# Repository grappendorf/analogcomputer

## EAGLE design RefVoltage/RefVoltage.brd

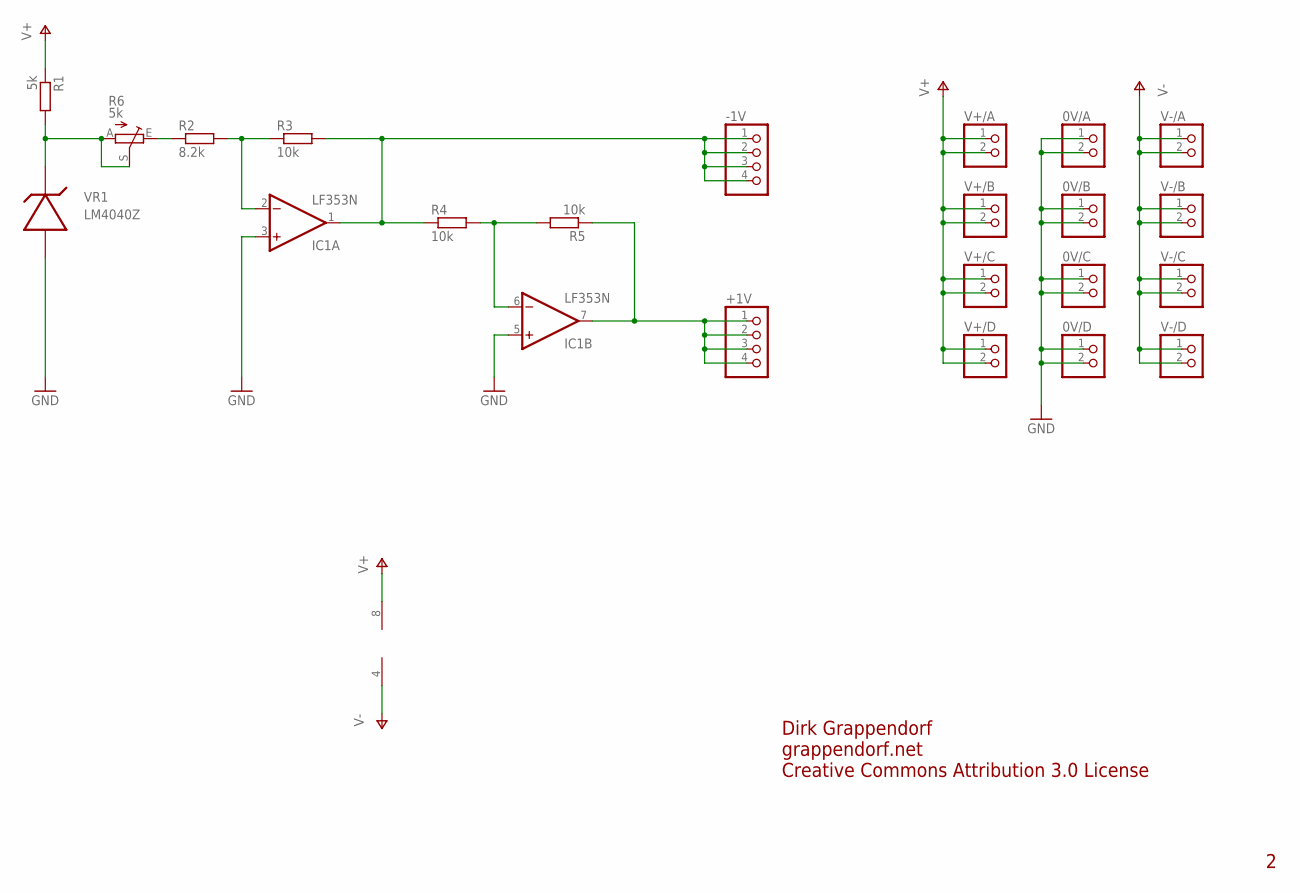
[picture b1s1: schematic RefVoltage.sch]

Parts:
0V/A, 0V/B, 0V/C, 0V/D: PINHD-1X2; 1X02
+1V: PINHD-1X4; 1X04
-1V: PINHD-1X4; 1X04
IC1: LF353N; DIL08
R1: 5k; 0207/7
R2: 8.2k; 0207/7
R3, R4, R5: 10k; 0207/7
R6: 5k; LI10
V+/A: PINHD-1X2; 1X02
V+/B: PINHD-1X2; 1X02
V+/C: PINHD-1X2; 1X02
V+/D: PINHD-1X2; 1X02
V-/A: PINHD-1X2; 1X02
V-/B: PINHD-1X2; 1X02
V-/C: PINHD-1X2; 1X02
V-/D: PINHD-1X2; 1X02
VR1: LM4040Z; TO92

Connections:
GND: 0V/A.1, 0V/A.2, 0V/B.1, 0V/B.2, 0V/C.1, 0V/C.2, 0V/D.1, 0V/D.2, IC1.3 (+IN), IC1.5 (+IN), VR1.3
unnamed: R1.2, R6.A, R6.S, VR1.2
unnamed: IC1.2 (-IN), R2.2, R3.1
unnamed: IC1.6 (-IN), R4.2, R5.2
unnamed: -1V.1, -1V.2, -1V.3, -1V.4, IC1.1 (OUT), R3.2, R4.1
unnamed: +1V.1, +1V.2, +1V.3, +1V.4, IC1.7 (OUT), R5.1
unnamed: R2.1, R6.E
V+: IC1.8 (V+), R1.1, V+/A.1, V+/A.2, V+/B.1, V+/B.2, V+/C.1, V+/C.2, V+/D.1, V+/D.2
V-: IC1.4 (V-), V-/A.1, V-/A.2, V-/B.1, V-/B.2, V-/C.1, V-/C.2, V-/D.1, V-/D.2

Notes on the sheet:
Dirk Grappendorf
grappendorf.net
Creative Commons Attribution 3.0 License

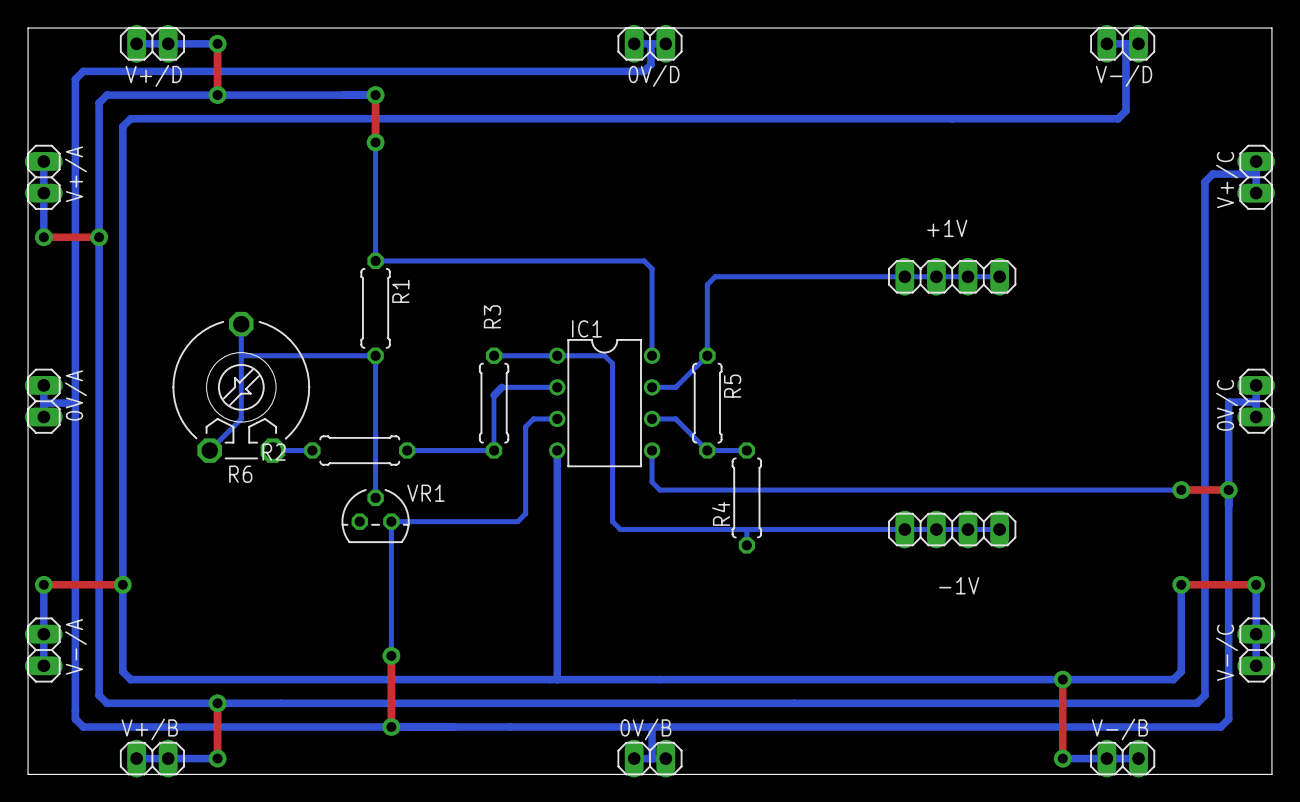
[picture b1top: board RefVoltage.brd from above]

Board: 2 copper layers, 100.0 x 60.0 mm, 22 parts (0 on the bottom side), 9 nets.

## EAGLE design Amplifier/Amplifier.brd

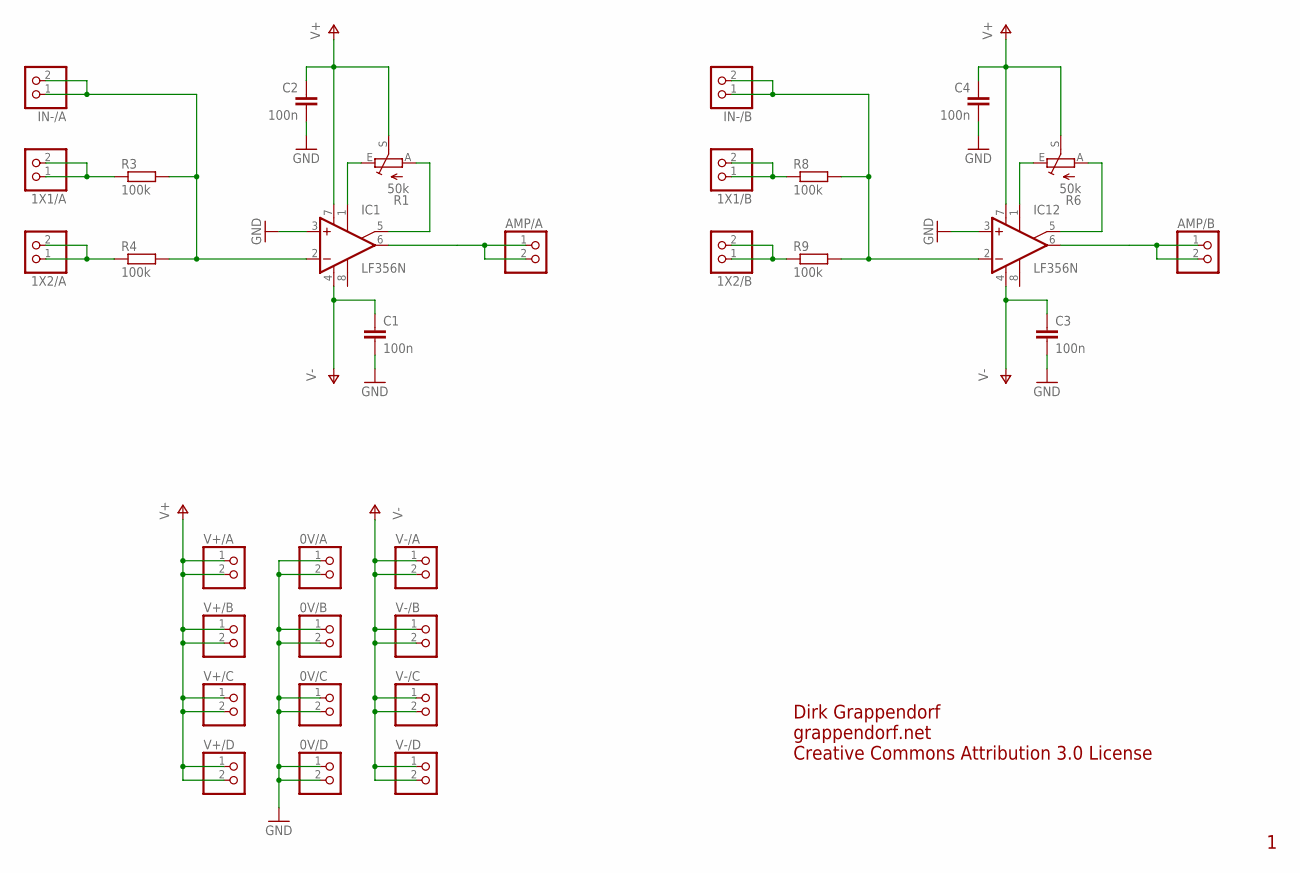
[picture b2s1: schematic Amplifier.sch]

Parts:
0V/A, 0V/B, 0V/C, 0V/D, 1X1/A, 1X1/B, 1X2/A, 1X2/B: PINHD-1X2; 1X02
AMP/A: PINHD-1X2; 1X02
AMP/B: PINHD-1X2; 1X02
C1, C2, C3, C4: 100n; C025-025X050
IC1, IC12: LF356N; DIL08
IN-/A: PINHD-1X2; 1X02
IN-/B: PINHD-1X2; 1X02
R1, R6: 50k; LI15
R3, R4, R8, R9: 100k; 0207/7
V+/A: PINHD-1X2; 1X02
V+/B: PINHD-1X2; 1X02
V+/C: PINHD-1X2; 1X02
V+/D: PINHD-1X2; 1X02
V-/A: PINHD-1X2; 1X02
V-/B: PINHD-1X2; 1X02
V-/C: PINHD-1X2; 1X02
V-/D: PINHD-1X2; 1X02

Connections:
GND: 0V/A.1, 0V/A.2, 0V/B.1, 0V/B.2, 0V/C.1, 0V/C.2, 0V/D.1, 0V/D.2, C1.2, C2.2, C3.2, C4.2, IC1.3 (+IN), IC12.3 (+IN)
unnamed: IC1.1 (ON1), R1.E
unnamed: IC1.5 (ON2), R1.A
unnamed: AMP/A.1, AMP/A.2, IC1.6 (OUT)
unnamed: 1X2/A.1, 1X2/A.2, R4.1
unnamed: 1X1/A.1, 1X1/A.2, R3.1
unnamed: IC1.2 (-IN), IN-/A.1, IN-/A.2, R3.2, R4.2
unnamed: IC12.1 (ON1), R6.E
unnamed: IC12.5 (ON2), R6.A
unnamed: AMP/B.1, AMP/B.2, IC12.6 (OUT)
unnamed: 1X1/B.1, 1X1/B.2, R8.1
unnamed: 1X2/B.1, 1X2/B.2, R9.1
unnamed: IC12.2 (-IN), IN-/B.1, IN-/B.2, R8.2, R9.2
V+: C2.1, C4.1, IC1.7 (V+), IC12.7 (V+), R1.S, R6.S, V+/A.1, V+/A.2, V+/B.1, V+/B.2, V+/C.1, V+/C.2, V+/D.1, V+/D.2
V-: C1.1, C3.1, IC1.4 (V-), IC12.4 (V-), V-/A.1, V-/A.2, V-/B.1, V-/B.2, V-/C.1, V-/C.2, V-/D.1, V-/D.2

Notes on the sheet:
Dirk Grappendorf
grappendorf.net
Creative Commons Attribution 3.0 License

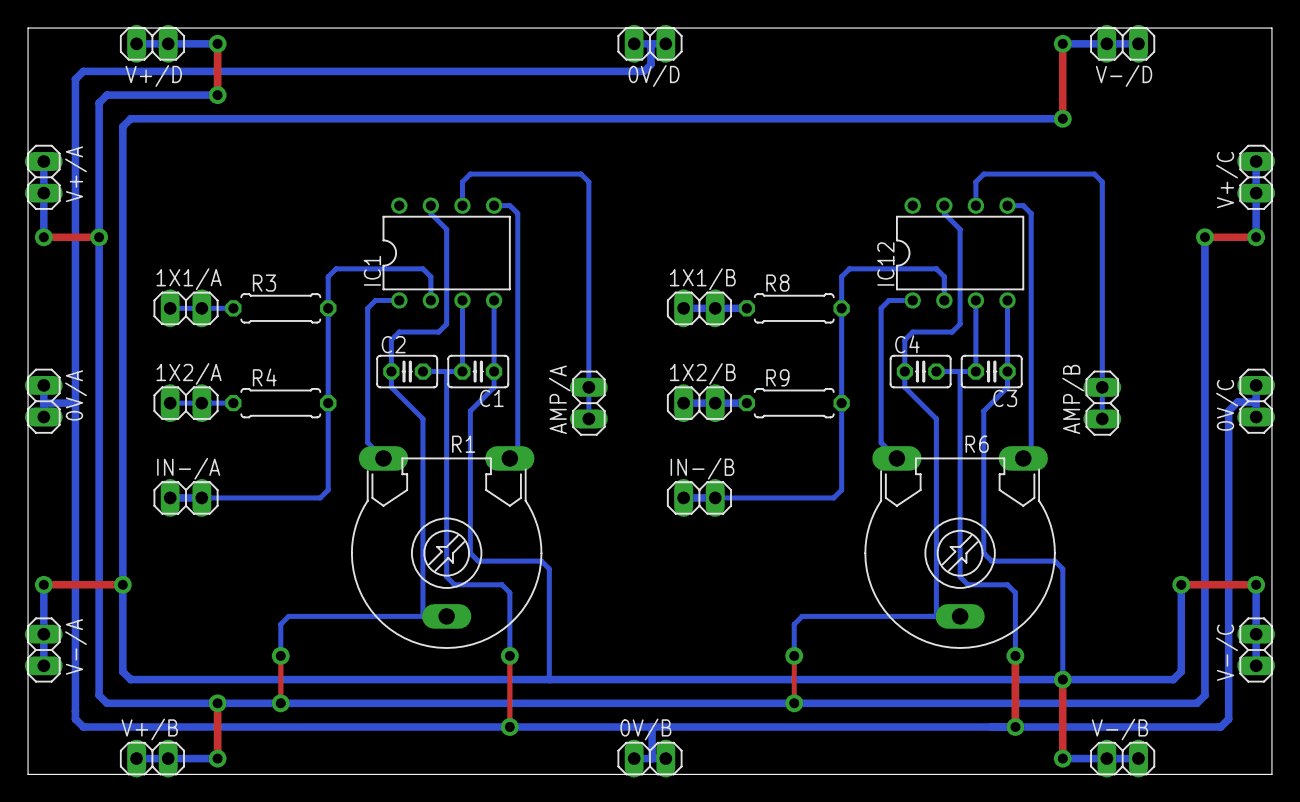
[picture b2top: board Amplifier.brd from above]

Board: 2 copper layers, 100.0 x 60.0 mm, 32 parts (0 on the bottom side), 15 nets.

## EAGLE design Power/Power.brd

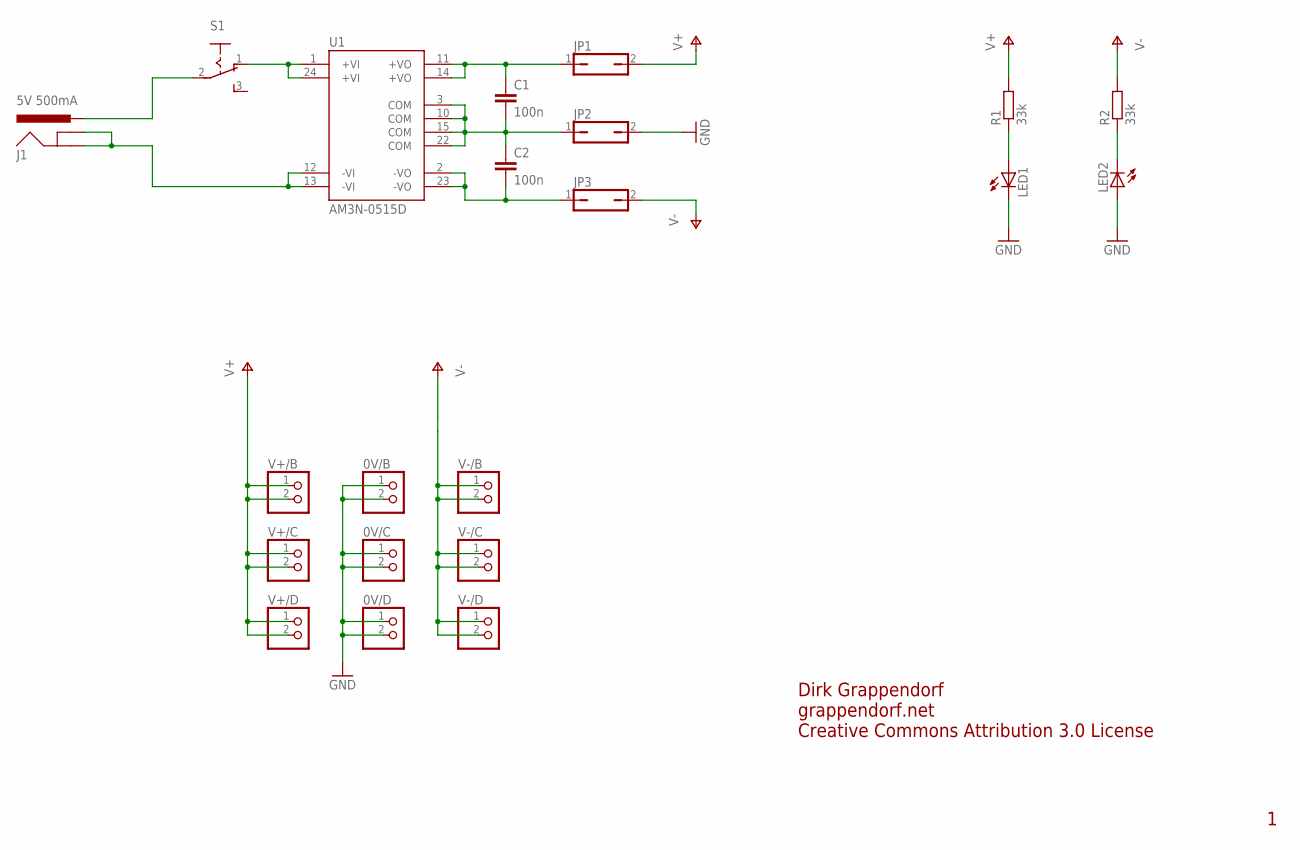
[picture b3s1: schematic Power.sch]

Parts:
0V/B, 0V/C, 0V/D: PINHD-1X2; 1X02
C1, C2: 100n; C025-025X050
J1: 5V 500mA; POWER_JACK_PTH
JP1, JP2, JP3: JP1Q; JP1
LED1, LED2: LED3MM
R1, R2: 33k; 0207/7
S1: REICHELT-SS_13ASP
U1: AM3N-0515D; AM3N_DIL24
V+/B: PINHD-1X2; 1X02
V+/C: PINHD-1X2; 1X02
V+/D: PINHD-1X2; 1X02
V-/B: PINHD-1X2; 1X02
V-/C: PINHD-1X2; 1X02
V-/D: PINHD-1X2; 1X02

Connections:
+VO: C1.1, JP1.1, U1.11 (+VO), U1.14 (+VO)
-VO: C2.2, JP3.1, U1.2 (-VO), U1.23 (-VO)
COM: C1.2, C2.1, JP2.1, U1.3 (COM), U1.10 (COM), U1.15 (COM), U1.22 (COM)
GND: 0V/B.1, 0V/B.2, 0V/C.1, 0V/C.2, 0V/D.1, 0V/D.2, JP2.2, LED1.K (C), LED2.A
unnamed: J1.PWR, S1.2
unnamed: J1.GND, J1.GNDBREAK, U1.12 (-VI), U1.13 (-VI)
unnamed: LED1.A, R1.1
unnamed: LED2.K (C), R2.1
unnamed: S1.1 (O), U1.1 (+VI), U1.24 (+VI)
V+: JP1.2, R1.2, V+/B.1, V+/B.2, V+/C.1, V+/C.2, V+/D.1, V+/D.2
V-: JP3.2, R2.2, V-/B.1, V-/B.2, V-/C.1, V-/C.2, V-/D.1, V-/D.2

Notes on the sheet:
Dirk Grappendorf
grappendorf.net
Creative Commons Attribution 3.0 License

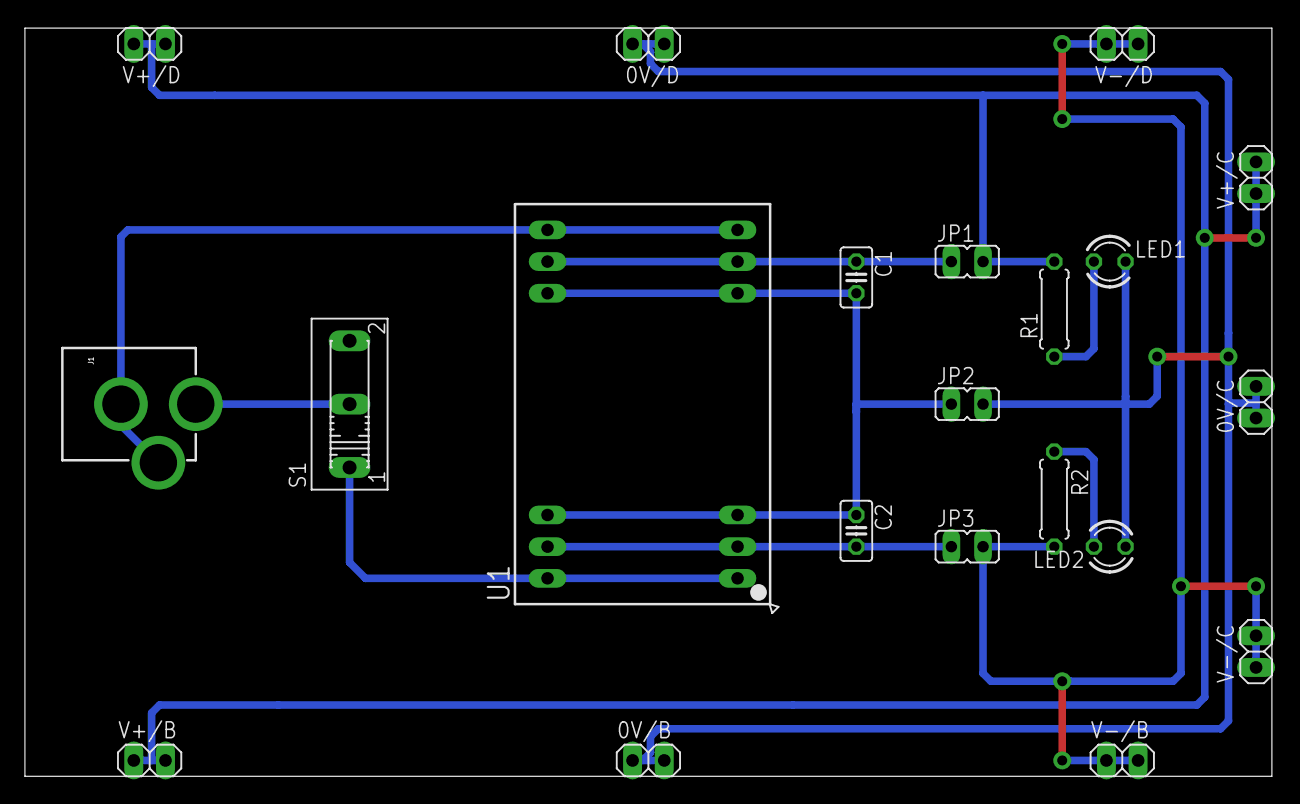
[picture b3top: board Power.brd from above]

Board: 2 copper layers, 100.0 x 60.0 mm, 21 parts (0 on the bottom side), 11 nets.

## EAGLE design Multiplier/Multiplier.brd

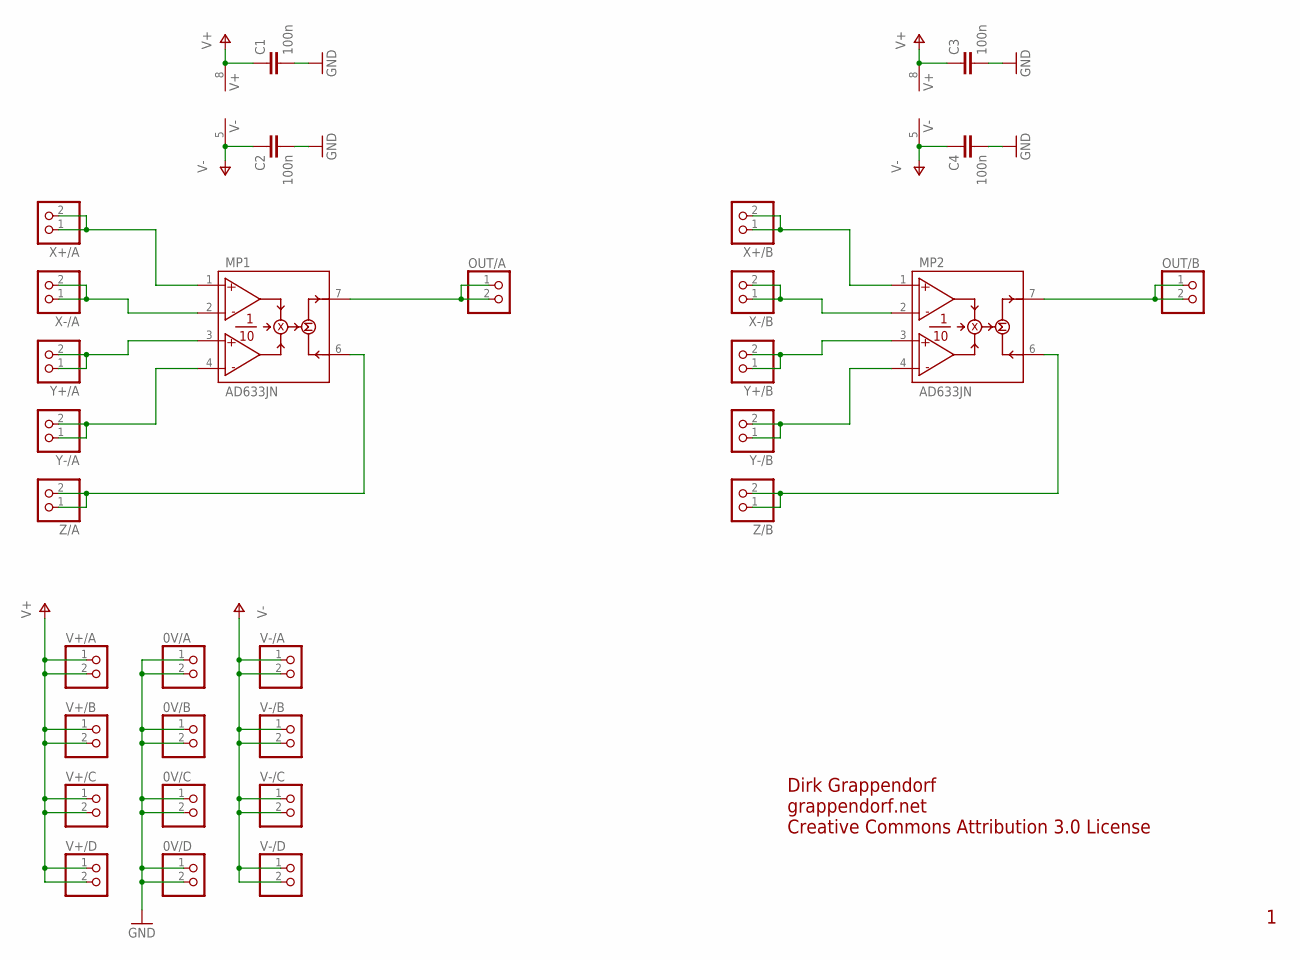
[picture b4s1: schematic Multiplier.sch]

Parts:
0V/A, 0V/B, 0V/C, 0V/D: PINHD-1X2; 1X02
C1, C2, C3, C4: 100n; C025-025X050
MP1, MP2: AD633JN; DIL08
OUT/A: PINHD-1X2; 1X02
OUT/B: PINHD-1X2; 1X02
V+/A: PINHD-1X2; 1X02
V+/B: PINHD-1X2; 1X02
V+/C: PINHD-1X2; 1X02
V+/D: PINHD-1X2; 1X02
V-/A: PINHD-1X2; 1X02
V-/B: PINHD-1X2; 1X02
V-/C: PINHD-1X2; 1X02
V-/D: PINHD-1X2; 1X02
X+/A: PINHD-1X2; 1X02
X+/B: PINHD-1X2; 1X02
X-/A: PINHD-1X2; 1X02
X-/B: PINHD-1X2; 1X02
Y+/A: PINHD-1X2; 1X02
Y+/B: PINHD-1X2; 1X02
Y-/A: PINHD-1X2; 1X02
Y-/B: PINHD-1X2; 1X02
Z/A: PINHD-1X2; 1X02
Z/B: PINHD-1X2; 1X02

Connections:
GND: 0V/A.1, 0V/A.2, 0V/B.1, 0V/B.2, 0V/C.1, 0V/C.2, 0V/D.1, 0V/D.2, C1.2, C2.2, C3.2, C4.2
unnamed: MP1.2 (X2), X-/A.1, X-/A.2
unnamed: MP1.1 (X1), X+/A.1, X+/A.2
unnamed: MP1.7 (W), OUT/A.1, OUT/A.2
unnamed: MP1.3 (Y1), Y+/A.1, Y+/A.2
unnamed: MP1.4 (Y2), Y-/A.1, Y-/A.2
unnamed: MP1.6 (Z), Z/A.1, Z/A.2
unnamed: MP2.2 (X2), X-/B.1, X-/B.2
unnamed: MP2.1 (X1), X+/B.1, X+/B.2
unnamed: MP2.3 (Y1), Y+/B.1, Y+/B.2
unnamed: MP2.4 (Y2), Y-/B.1, Y-/B.2
unnamed: MP2.6 (Z), Z/B.1, Z/B.2
unnamed: MP2.7 (W), OUT/B.1, OUT/B.2
V+: C1.1, C3.1, MP1.8 (V+), MP2.8 (V+), V+/A.1, V+/A.2, V+/B.1, V+/B.2, V+/C.1, V+/C.2, V+/D.1, V+/D.2
V-: C2.1, C4.1, MP1.5 (V-), MP2.5 (V-), V-/A.1, V-/A.2, V-/B.1, V-/B.2, V-/C.1, V-/C.2, V-/D.1, V-/D.2

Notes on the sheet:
Dirk Grappendorf
grappendorf.net
Creative Commons Attribution 3.0 License

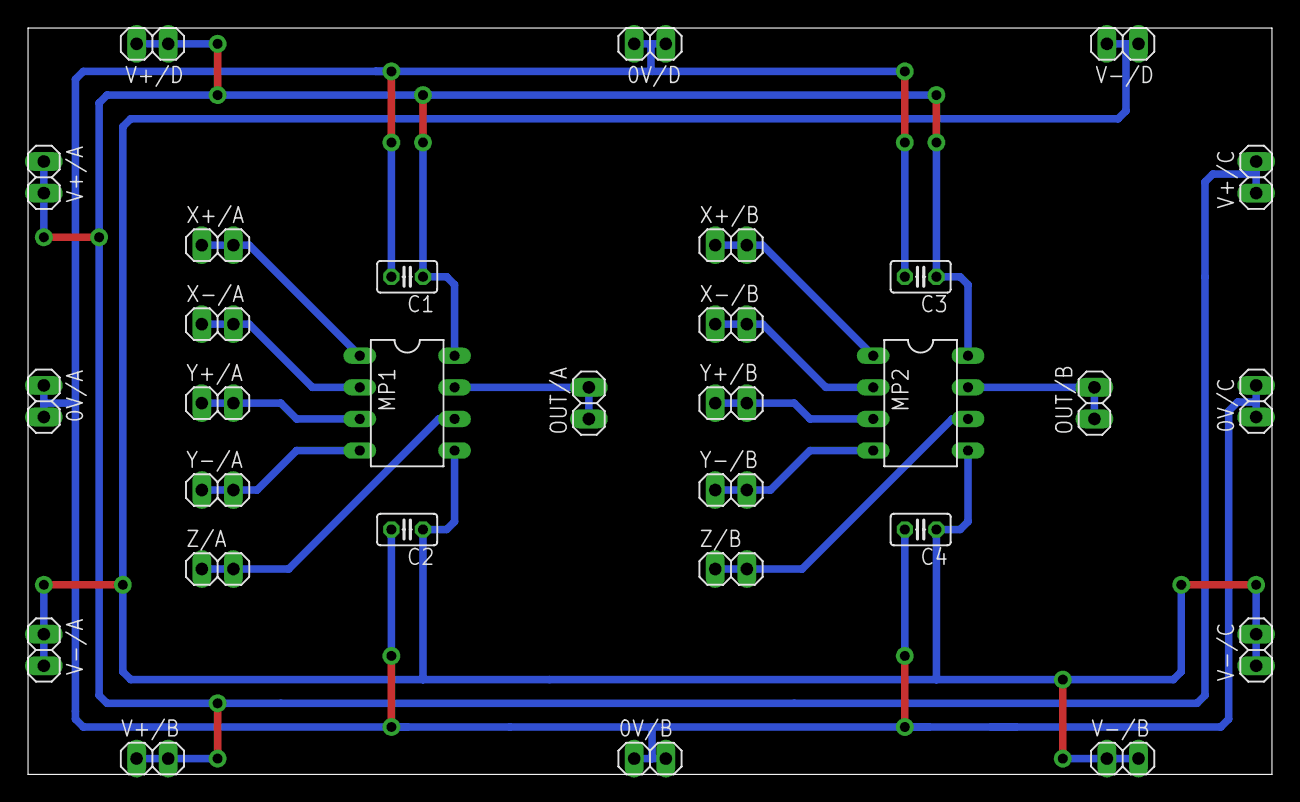
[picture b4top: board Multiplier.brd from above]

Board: 2 copper layers, 100.0 x 60.0 mm, 30 parts (0 on the bottom side), 15 nets.

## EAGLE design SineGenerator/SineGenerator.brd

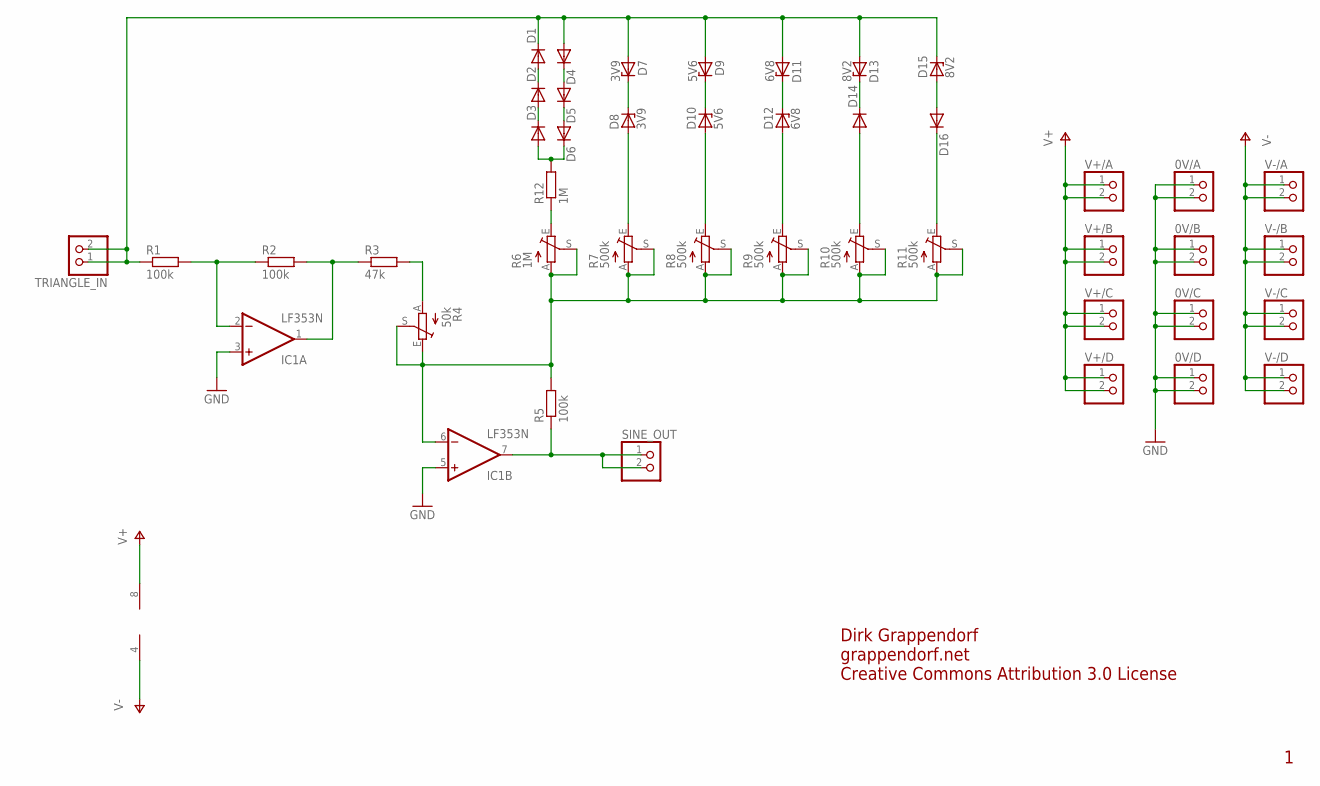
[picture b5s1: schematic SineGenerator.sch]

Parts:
0V/A, 0V/B, 0V/C, 0V/D: PINHD-1X2; 1X02
D1, D2, D3, D4, D5, D6, D14, D16: DIODE1N4148; DIODE-1N4148
D7, D8: 3V9; DO34Z7
D9, D10: 5V6; DO34Z7
D11, D12: 6V8; DO34Z7
D13, D15: 8V2; DO34Z7
IC1: LF353N; DIL08
R1, R2, R5: 100k; 0207/7
R3: 47k; 0207/7
R4: 50k; LI15
R6: 1M; ST15
R7, R8, R9, R10, R11: 500k; ST15
R12: 1M; 0207/7
SINE_OUT: PINHD-1X2; 1X02
TRIANGLE_IN: PINHD-1X2; 1X02
V+/A: PINHD-1X2; 1X02
V+/B: PINHD-1X2; 1X02
V+/C: PINHD-1X2; 1X02
V+/D: PINHD-1X2; 1X02
V-/A: PINHD-1X2; 1X02
V-/B: PINHD-1X2; 1X02
V-/C: PINHD-1X2; 1X02
V-/D: PINHD-1X2; 1X02

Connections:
GND: 0V/A.1, 0V/A.2, 0V/B.1, 0V/B.2, 0V/C.1, 0V/C.2, 0V/D.1, 0V/D.2, IC1.3 (+IN), IC1.5 (+IN)
unnamed: IC1.2 (-IN), R1.2, R2.1
unnamed: D9.C, D10.C
unnamed: IC1.1 (OUT), R2.2, R3.1
unnamed: D10.A, R8.E
unnamed: R3.2, R4.A
unnamed: D11.C, D12.C
unnamed: IC1.6 (-IN), R4.E, R4.S, R5.2, R6.A, R6.S, R7.A, R7.S, R8.A, R8.S, R9.A, R9.S, R10.A, R10.S, R11.A, R11.S
unnamed: IC1.7 (OUT), R5.1, SINE_OUT.1, SINE_OUT.2
unnamed: D1.C, D4.A, D7.A, D9.A, D11.A, D13.A, D15.C, R1.1, TRIANGLE_IN.1, TRIANGLE_IN.2
unnamed: D1.A, D2.C
unnamed: D2.A, D3.C
unnamed: D3.A, D6.C, R12.2
unnamed: D5.C, D6.A
unnamed: D4.C, D5.A
unnamed: R6.E, R12.1
unnamed: D7.C, D8.C
unnamed: D8.A, R7.E
unnamed: D12.A, R9.E
unnamed: D13.C, D14.C
unnamed: D14.A, R10.E
unnamed: D15.A, D16.A
unnamed: D16.C, R11.E
V+: IC1.8 (V+), V+/A.1, V+/A.2, V+/B.1, V+/B.2, V+/C.1, V+/C.2, V+/D.1, V+/D.2
V-: IC1.4 (V-), V-/A.1, V-/A.2, V-/B.1, V-/B.2, V-/C.1, V-/C.2, V-/D.1, V-/D.2

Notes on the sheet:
Dirk Grappendorf
grappendorf.net
Creative Commons Attribution 3.0 License

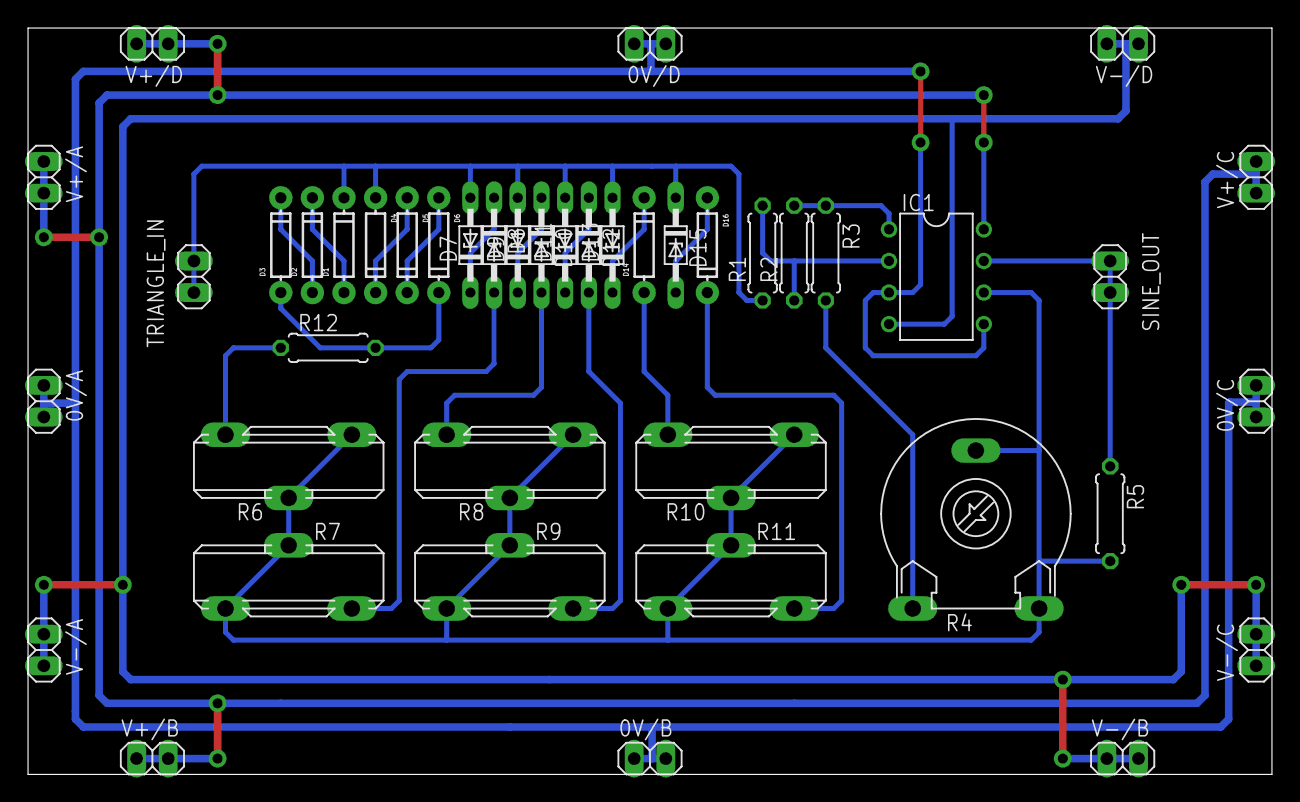
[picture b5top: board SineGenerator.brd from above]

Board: 2 copper layers, 100.0 x 60.0 mm, 43 parts (0 on the bottom side), 25 nets.

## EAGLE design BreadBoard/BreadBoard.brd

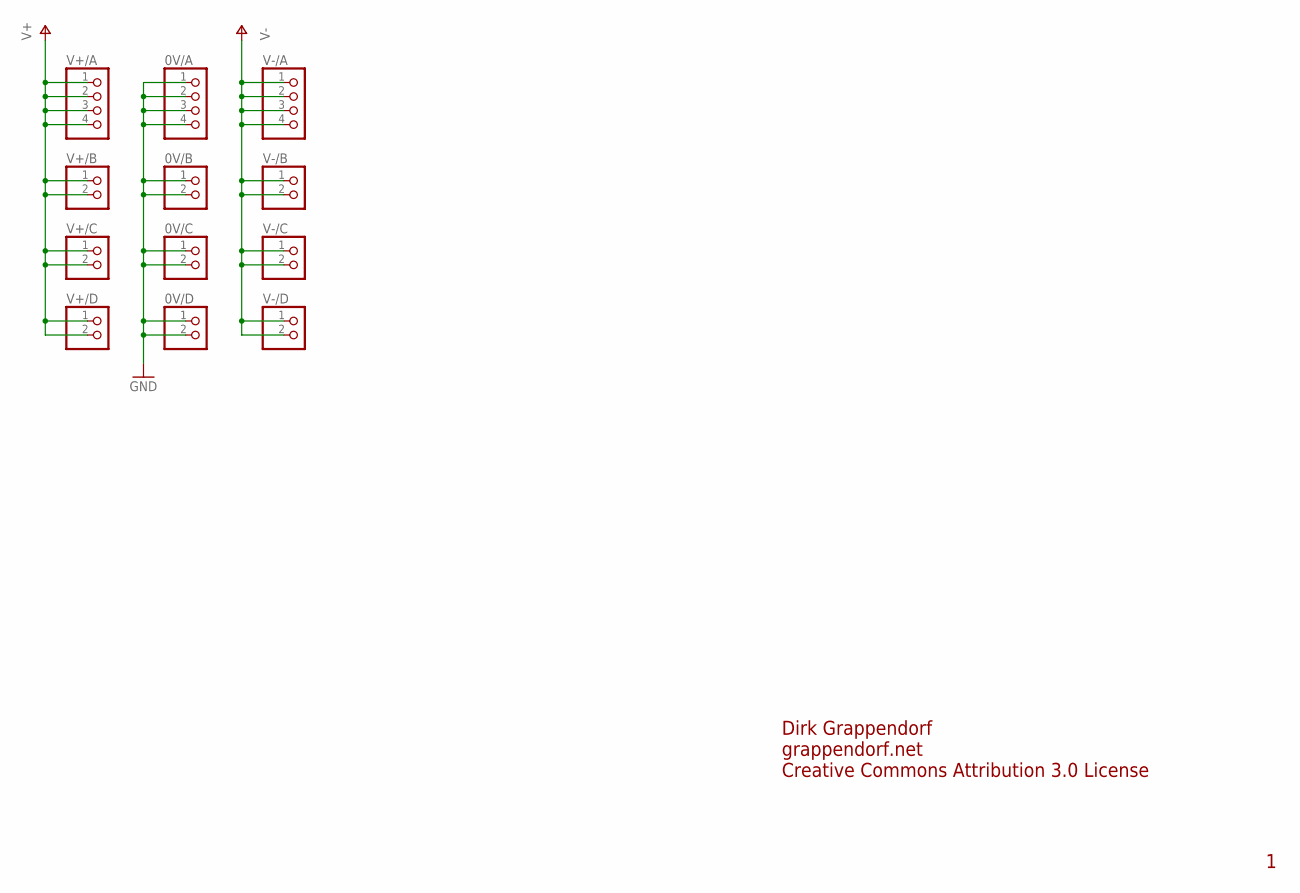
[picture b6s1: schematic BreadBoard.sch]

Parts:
0V/A: PINHD-1X4; 1X04
0V/B, 0V/C, 0V/D: PINHD-1X2; 1X02
V+/A: PINHD-1X4; 1X04
V+/B: PINHD-1X2; 1X02
V+/C: PINHD-1X2; 1X02
V+/D: PINHD-1X2; 1X02
V-/A: PINHD-1X4; 1X04
V-/B: PINHD-1X2; 1X02
V-/C: PINHD-1X2; 1X02
V-/D: PINHD-1X2; 1X02

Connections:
GND: 0V/A.1, 0V/A.2, 0V/A.3, 0V/A.4, 0V/B.1, 0V/B.2, 0V/C.1, 0V/C.2, 0V/D.1, 0V/D.2
V+: V+/A.1, V+/A.2, V+/A.3, V+/A.4, V+/B.1, V+/B.2, V+/C.1, V+/C.2, V+/D.1, V+/D.2
V-: V-/A.1, V-/A.2, V-/A.3, V-/A.4, V-/B.1, V-/B.2, V-/C.1, V-/C.2, V-/D.1, V-/D.2

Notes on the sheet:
Dirk Grappendorf
grappendorf.net
Creative Commons Attribution 3.0 License

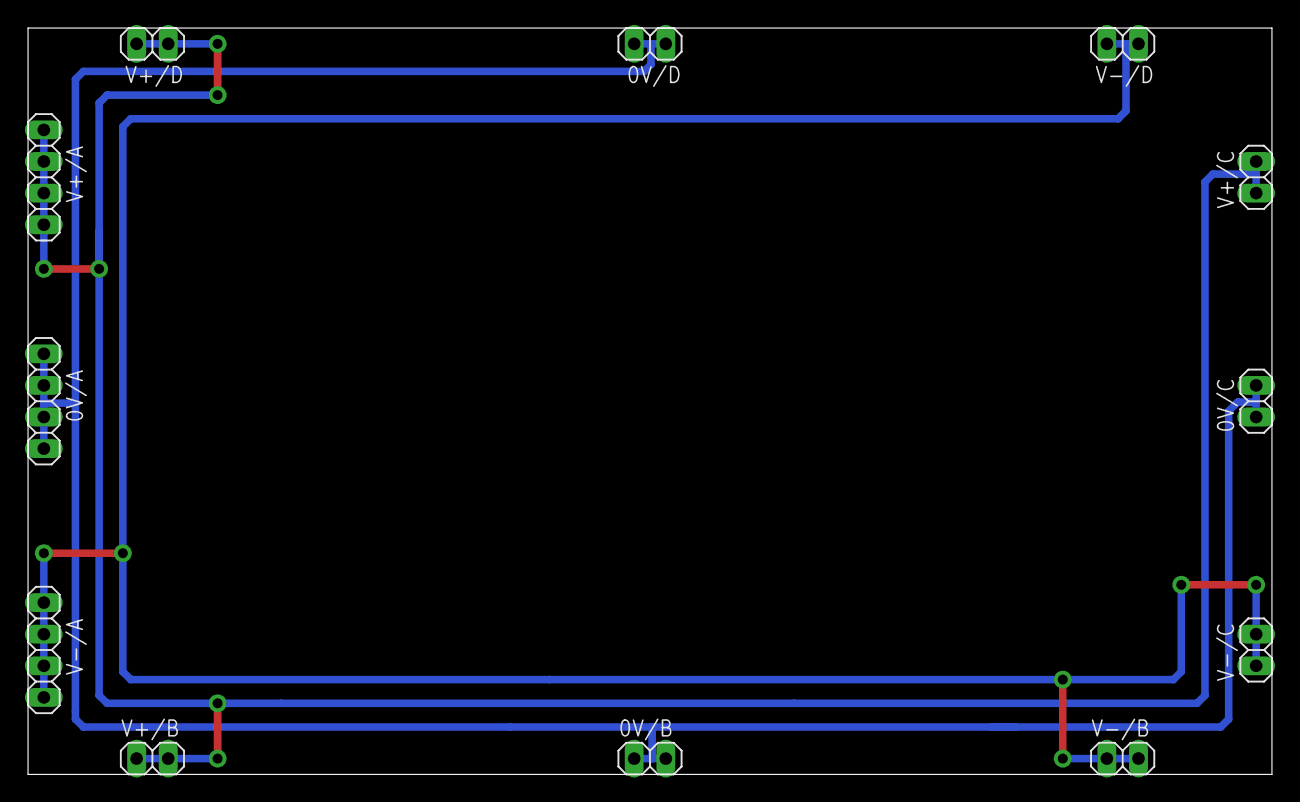
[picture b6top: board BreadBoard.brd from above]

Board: 2 copper layers, 100.0 x 60.0 mm, 12 parts (0 on the bottom side), 3 nets.

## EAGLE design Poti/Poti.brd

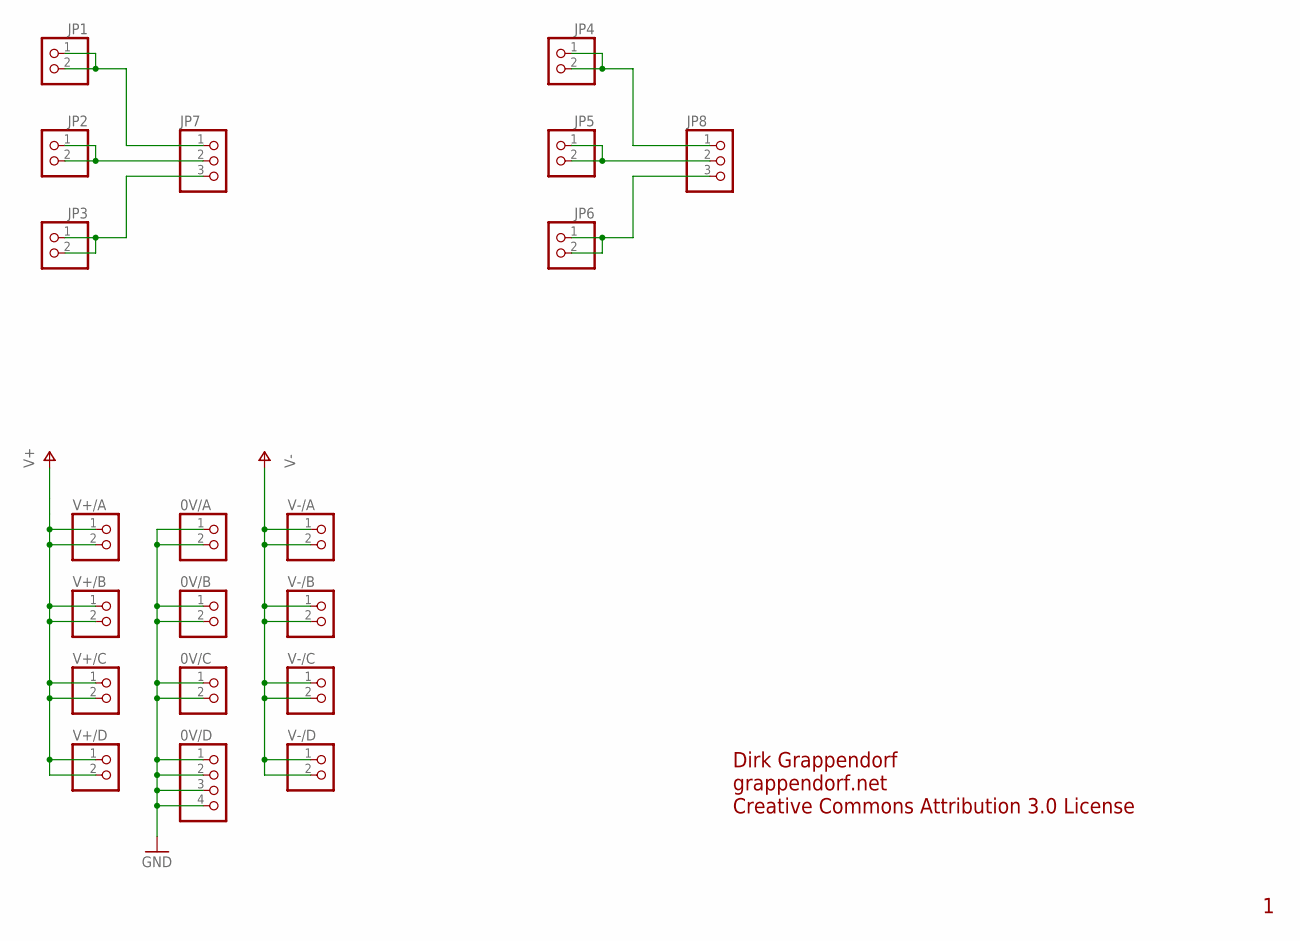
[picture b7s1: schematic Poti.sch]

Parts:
0V/A, 0V/B, 0V/C: PINHD-1X2; 1X02
0V/D: PINHD-1X4; 1X04
JP1, JP2, JP3, JP4, JP5, JP6: PINHD-1X2; 1X02
JP7, JP8: PINHD-1X3; 1X03
V+/A: PINHD-1X2; 1X02
V+/B: PINHD-1X2; 1X02
V+/C: PINHD-1X2; 1X02
V+/D: PINHD-1X2; 1X02
V-/A: PINHD-1X2; 1X02
V-/B: PINHD-1X2; 1X02
V-/C: PINHD-1X2; 1X02
V-/D: PINHD-1X2; 1X02

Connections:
0V/A: 0V/A.1, 0V/A.2, 0V/B.1, 0V/B.2, 0V/C.1, 0V/C.2, 0V/D.1, 0V/D.2, 0V/D.3, 0V/D.4
unnamed: JP2.1, JP2.2, JP7.2
unnamed: JP1.1, JP1.2, JP7.1
unnamed: JP3.1, JP3.2, JP7.3
unnamed: JP5.1, JP5.2, JP8.2
unnamed: JP4.1, JP4.2, JP8.1
unnamed: JP6.1, JP6.2, JP8.3
V+: V+/A.1, V+/A.2, V+/B.1, V+/B.2, V+/C.1, V+/C.2, V+/D.1, V+/D.2
V-: V-/A.1, V-/A.2, V-/B.1, V-/B.2, V-/C.1, V-/C.2, V-/D.1, V-/D.2

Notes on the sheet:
Dirk Grappendorf
grappendorf.net
Creative Commons Attribution 3.0 License

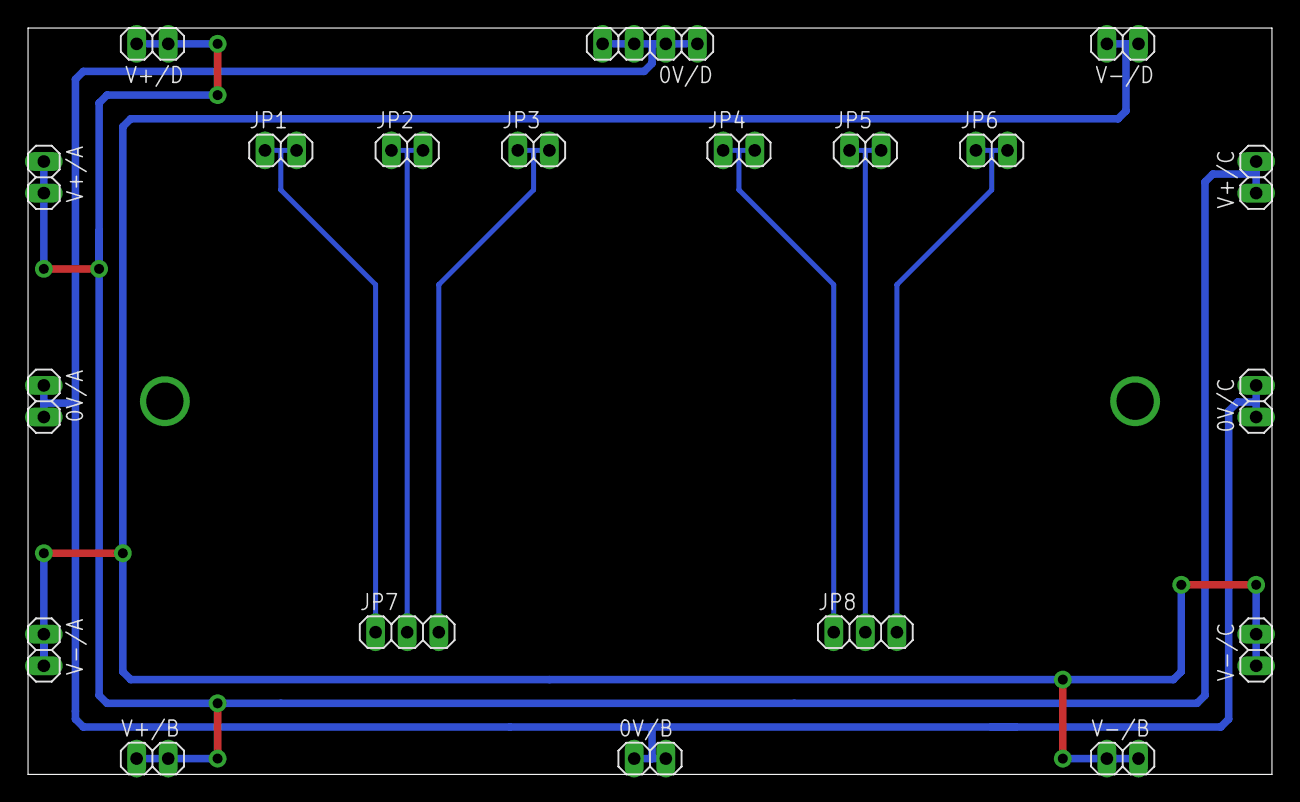
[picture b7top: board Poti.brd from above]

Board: 2 copper layers, 100.0 x 60.0 mm, 20 parts (0 on the bottom side), 9 nets.

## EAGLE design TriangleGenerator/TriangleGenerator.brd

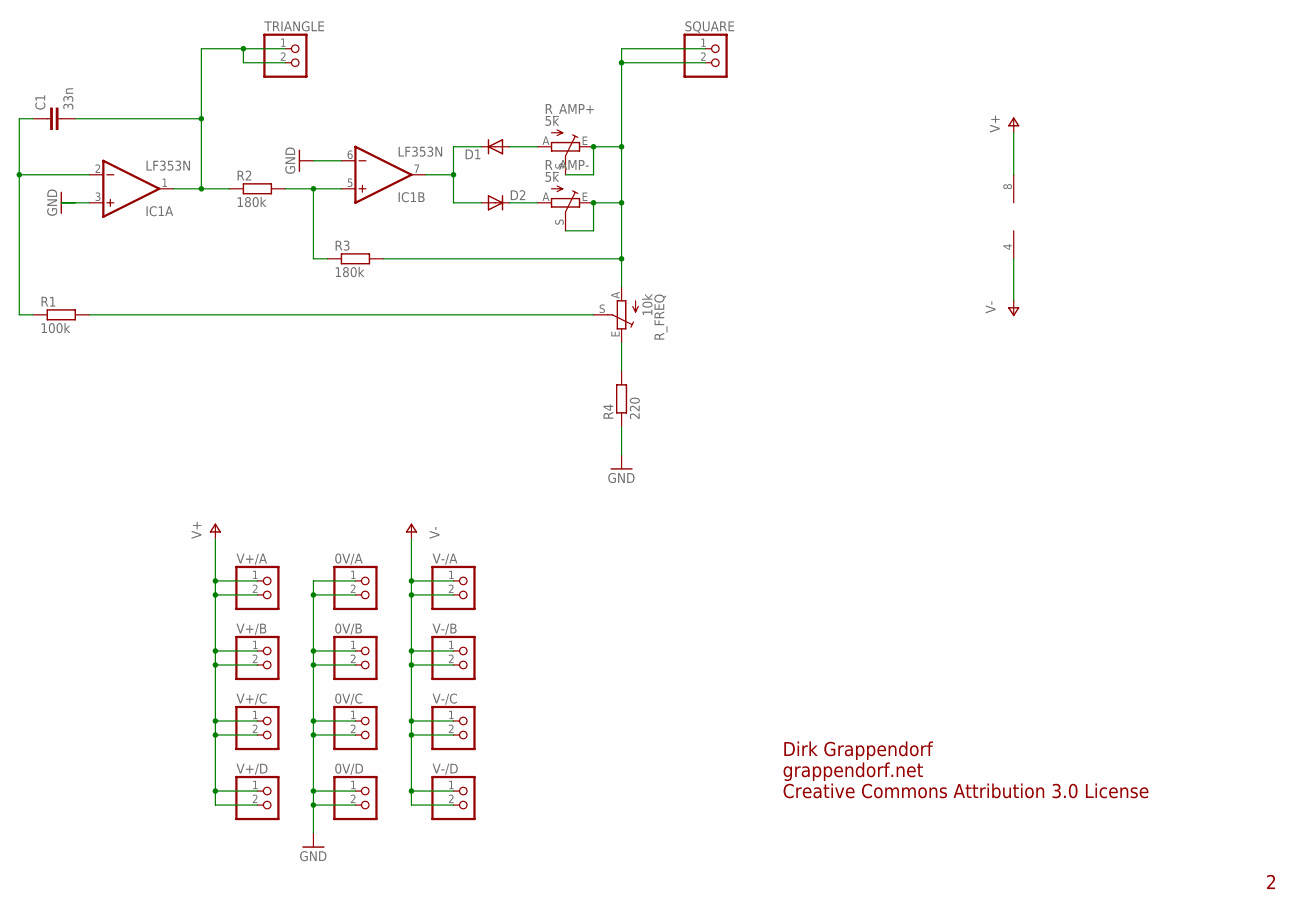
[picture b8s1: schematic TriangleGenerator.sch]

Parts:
0V/A, 0V/B, 0V/C, 0V/D: PINHD-1X2; 1X02
C1: 33n; C025-025X050
D1, D2: DIODE1N4148; DIODE-1N4148
IC1: LF353N; DIL08
R1: 100k; 0207/7
R2, R3: 180k; 0207/7
R4: 220; 0207/7
R_AMP+: 5k; LI15
R_AMP-: 5k; LI15
R_FREQ: 10k; LI15
SQUARE: PINHD-1X2; 1X02
TRIANGLE: PINHD-1X2; 1X02
V+/A: PINHD-1X2; 1X02
V+/B: PINHD-1X2; 1X02
V+/C: PINHD-1X2; 1X02
V+/D: PINHD-1X2; 1X02
V-/A: PINHD-1X2; 1X02
V-/B: PINHD-1X2; 1X02
V-/C: PINHD-1X2; 1X02
V-/D: PINHD-1X2; 1X02

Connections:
GND: 0V/A.1, 0V/A.2, 0V/B.1, 0V/B.2, 0V/C.1, 0V/C.2, 0V/D.1, 0V/D.2, IC1.3 (+IN), IC1.6 (-IN), R4.1
unnamed: C1.1, IC1.2 (-IN), R1.1
unnamed: C1.2, IC1.1 (OUT), R2.1, TRIANGLE.1, TRIANGLE.2
unnamed: IC1.5 (+IN), R2.2, R3.1
unnamed: D1.C, D2.A, IC1.7 (OUT)
unnamed: D1.A, R_AMP+.A
unnamed: D2.C, R_AMP-.A
unnamed: R3.2, R_AMP+.E, R_AMP+.S, R_AMP-.E, R_AMP-.S, R_FREQ.A, SQUARE.1, SQUARE.2
unnamed: R1.2, R_FREQ.S
unnamed: R4.2, R_FREQ.E
V+: IC1.8 (V+), V+/A.1, V+/A.2, V+/B.1, V+/B.2, V+/C.1, V+/C.2, V+/D.1, V+/D.2
V-: IC1.4 (V-), V-/A.1, V-/A.2, V-/B.1, V-/B.2, V-/C.1, V-/C.2, V-/D.1, V-/D.2

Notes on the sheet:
Dirk Grappendorf
grappendorf.net
Creative Commons Attribution 3.0 License
